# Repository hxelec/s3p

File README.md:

Haase Industries S3P boards: Arduino IDE code and KiCad schematic.

I'll comment the Arduino sketches properly in a few weeks, but,
meanwhile, ask me anything about the code or the schematic on my
YouTube video, and I'll be sure to respond to it.

Here's the video about this project:
https://youtu.be/9oY4NeJDy-g

Thanks to PCBWay for sponsoring this project! Get $5 of New User Free Credit by following this link - https://pcbway.com/g/x5f10h

PCBWay is one of the most experienced PCB manufacturers in China, consider them your one-stop solution that offers PCB fabrication, turn-key PCB Assembly, PCB design, 3D printing, and CNC machining services.

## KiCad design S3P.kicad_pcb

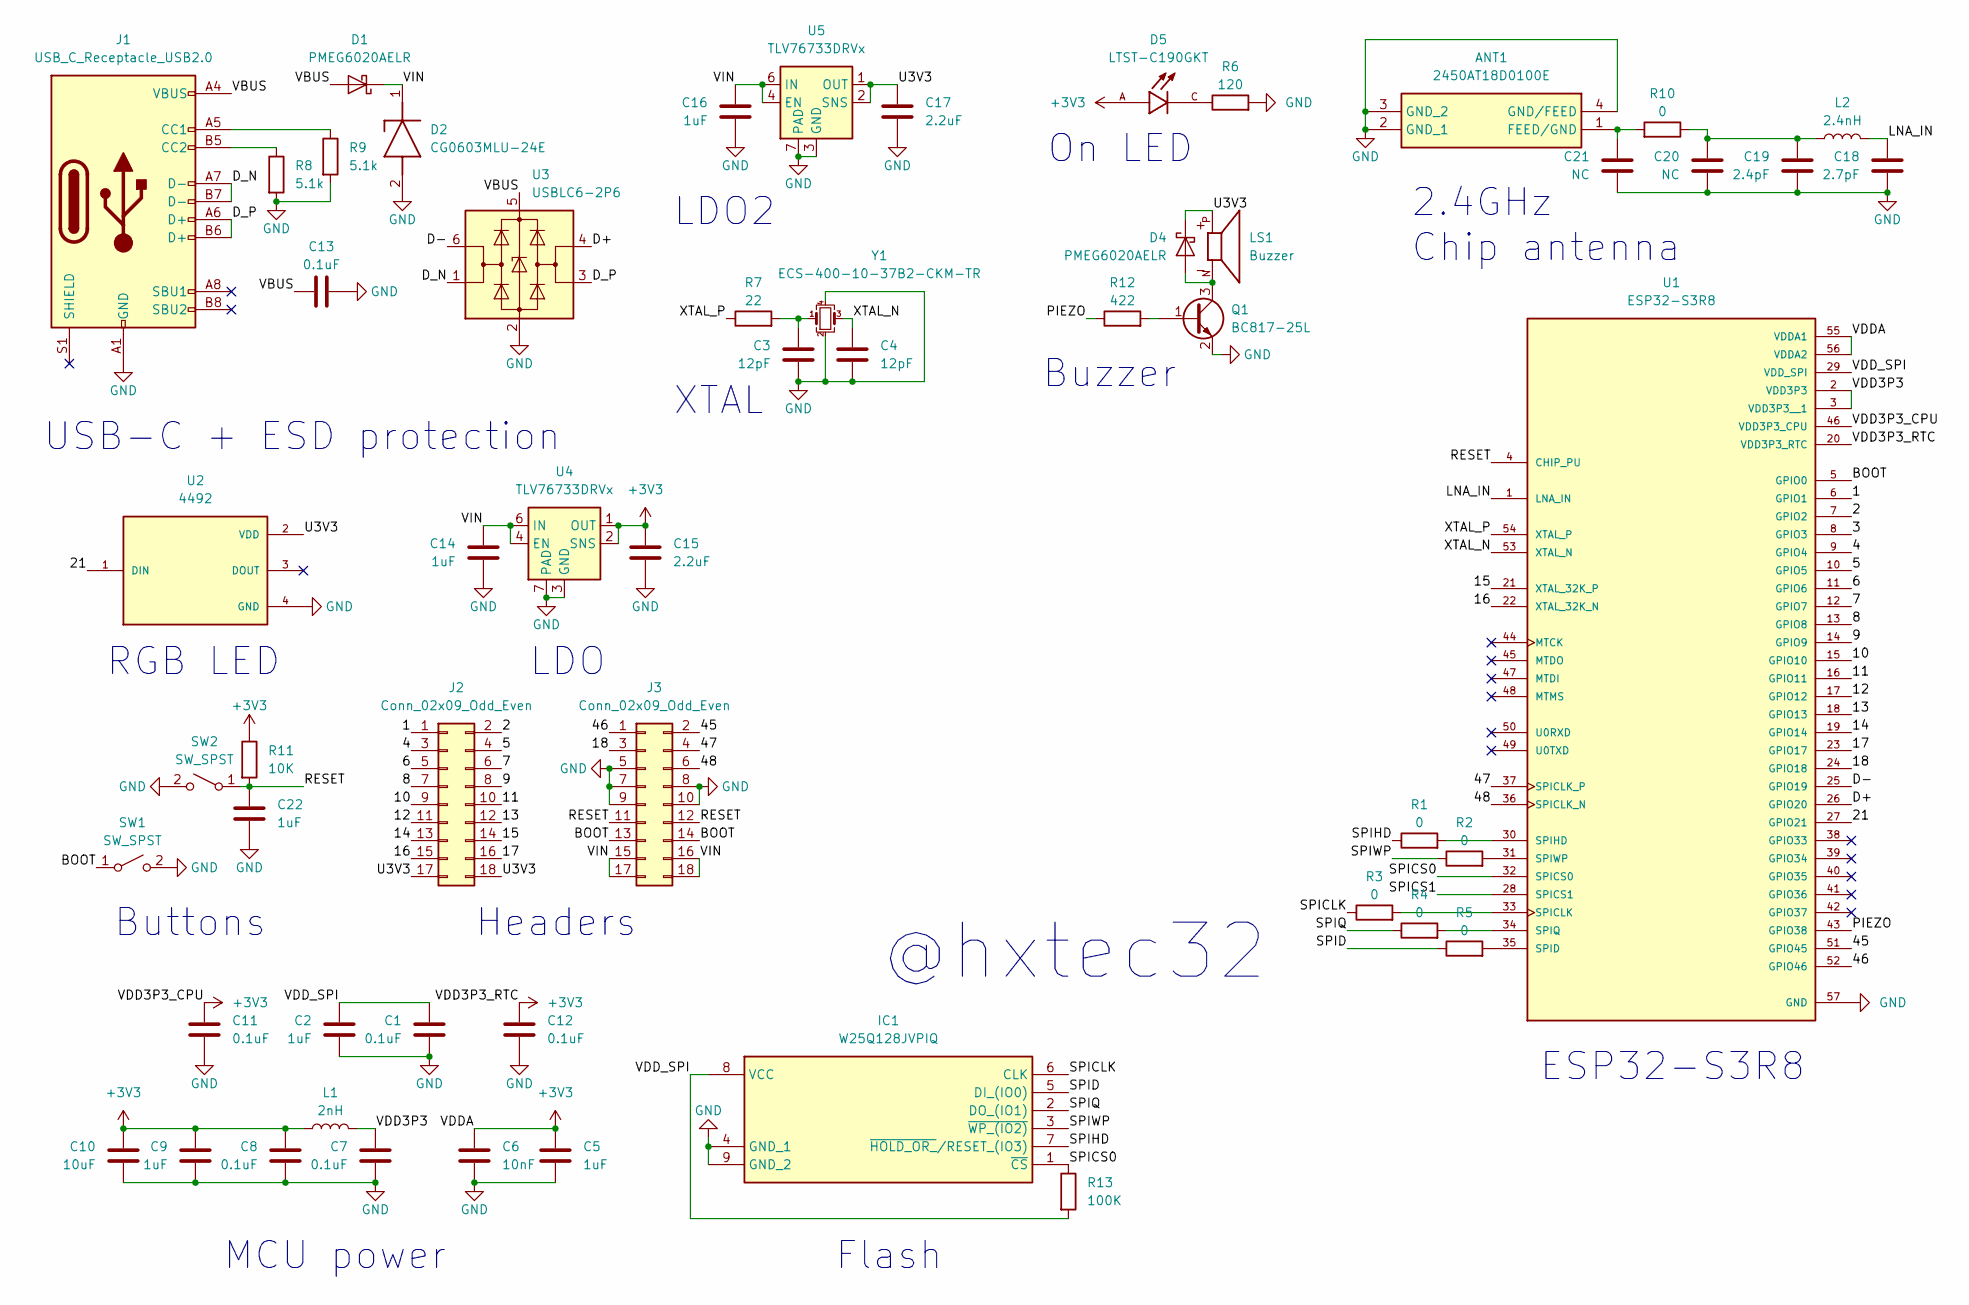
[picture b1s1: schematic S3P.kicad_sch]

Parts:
ANT1: 2450AT18D0100E; Manufacturer_Part_Number 2450AT18D0100E; Mouser Part Number 609-2450AT18D0100E
C1, C7, C8, C11, C12, C13: 0.1uF; R_0402_1005Metric
C2, C5, C9, C22: 1uF; R_0402_1005Metric
C3, C4: 12pF; R_0201_0603Metric
C6: 10nF; R_0201_0603Metric
C10: 10uF; R_0603_1608Metric
C14, C16: 1uF; R_0603_1608Metric
C15, C17: 2.2uF; R_0402_1005Metric
C18: 2.7pF; R_0201_0603Metric
C19: 2.4pF; R_0201_0603Metric
C20, C21: NC; R_0201_0603Metric
D1, D4: PMEG6020AELR; Nexperia_CFP3_SOD-123W
D2: CG0603MLU-24E; DIONC1608X55N; Manufacturer_Part_Number CG0603MLU-24E; Mouser Part Number 652-CG0603MLU-24E
D5: LTST-C190GKT; LEDC1608X35N
IC1: W25Q128JVPIQ; SON127P600X500X80-9N-D; Manufacturer_Part_Number W25Q128JVPIQ; Mouser Part Number 454-W25Q128JVPIQ
J1: USB_C_Receptacle_USB2.0; USB_C_Receptacle_GCT_USB4105-xx-A_16P_TopMnt_Horizontal
J2, J3: Conn_02x09_Odd_Even; PinHeader_2x09_P2.54mm_Vertical
L1: 2nH; L_0402_1005Metric
L2: 2.4nH; L_0201_0603Metric
LS1: Buzzer; XDCR_CMT-0525-75-SMT-TR; PARTREV 1.0
Q1: BC817-25L; SOT-23
R1, R2, R3, R4, R5, R10: 0; R_0201_0603Metric
R6: 120; R_0402_1005Metric
R7: 22; R_0402_1005Metric
R8, R9: 5.1k; R_0402_1005Metric
R11: 10K; R_0402_1005Metric
R12: 422; R_0402_1005Metric
R13: 100K; R_0201_0603Metric
SW1, SW2: SW_SPST; SW_SPST_PTS810
U1: ESP32-S3R8; QFN40P700X700X90-57N-D
U2: 4492; SK6805-EC15; PARTREV 14/10/19
U3: USBLC6-2P6; SOT-666
U4, U5: TLV76733DRVx; WSON-6-1EP_2x2mm_P0.65mm_EP1x1.6mm_ThermalVias
Y1: ECS-400-10-37B2-CKM-TR; Crystal_SMD_2016-4Pin_2.0x1.6mm

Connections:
+3V3: C5.1, C6.1, C8.1, C9.1, C10.1, C11.1, C12.1, C15.1, D5.A, L1.2, R11.1, U1.20 (VDD3P3_RTC), U1.46 (VDD3P3_CPU), U1.55 (VDDA1), U1.56 (VDDA2), U4.1 (OUT), U4.2 (SNS)
/1: J2.1, U1.6 (GPIO1)
/2: J2.2, U1.7 (GPIO2)
/3: U1.8 (GPIO3)
/4: J2.3, U1.9 (GPIO4)
/5: J2.4, U1.10 (GPIO5)
/6: J2.5, U1.11 (GPIO6)
/7: J2.6, U1.12 (GPIO7)
/8: J2.7, U1.13 (GPIO8)
/9: J2.8, U1.14 (GPIO9)
/10: J2.9, U1.15 (GPIO10)
/11: J2.10, U1.16 (GPIO11)
/12: J2.11, U1.17 (GPIO12)
/13: J2.12, U1.18 (GPIO13)
/14: J2.13, U1.19 (GPIO14)
/15: J2.14, U1.21 (XTAL_32K_P)
/16: J2.15, U1.22 (XTAL_32K_N)
/17: J2.16, U1.23 (GPIO17)
/18: J3.3, U1.24 (GPIO18)
/21: U1.27 (GPIO21), U2.1 (DIN)
/45: J3.2, U1.51 (GPIO45)
/46: J3.1, U1.52 (GPIO46)
/47: J3.4, U1.37 (SPICLK_P)
/48: J3.6, U1.36 (SPICLK_N)
/BOOT: J3.13, J3.14, SW1.1 (A), U1.5 (GPIO0)
/D+: U1.26 (GPIO20), U3.4 (I/O2)
/D-: U1.25 (GPIO19), U3.6 (I/O1)
/D_N: J1.A7 (D-), J1.B7 (D-), U3.1 (I/O1)
/D_P: J1.A6 (D+), J1.B6 (D+), U3.3 (I/O2)
/LNA_IN: C18.1, L2.1, U1.1 (LNA_IN)
/PIEZO: R12.1, U1.43 (GPIO38)
/RESET: C22.1, J3.11, J3.12, R11.2, SW2.1 (A), U1.4 (CHIP_PU)
/SPICLK: IC1.6 (CLK), R3.1
/SPICS0: IC1.1 (~CS), R13.1, U1.32 (SPICS0)
/SPICS1: U1.28 (SPICS1)
/SPID: IC1.5 (DI_(IO0)), R5.1
/SPIHD: IC1.7 (~HOLD_OR_/RESET_(IO3)), R1.1
/SPIQ: IC1.2 (DO_(IO1)), R4.1
/SPIWP: IC1.3 (~WP_(IO2)), R2.1
/U3V3: C17.1, D4.1 (K), J2.17, J2.18, LS1.P, U2.2 (VDD), U5.1 (OUT), U5.2 (SNS)
/VBUS: C13.1, D1.2 (A), J1.A4 (VBUS), J1.A9 (VBUS), J1.B4 (VBUS), J1.B9 (VBUS), U3.5 (VBUS)
/VDD3P3: C7.1, L1.1, U1.2 (VDD3P3), U1.3 (VDD3P3__1)
/VDD_SPI: C1.1, C2.1, IC1.8 (VCC), R13.2, U1.29 (VDD_SPI)
/VIN: C14.1, C16.1, D1.1 (K), D2.1 (K), J3.15, J3.16, J3.17, J3.18, U4.4 (EN), U4.6 (IN), U5.4 (EN), U5.6 (IN)
/XTAL_N: C4.1, U1.53 (XTAL_N), Y1.3
/XTAL_P: R7.1, U1.54 (XTAL_P)
GND: ANT1.2 (GND_1), ANT1.3 (GND_2), ANT1.4 (GND/FEED), C1.2, C2.2, C3.2, C4.2, C5.2, C6.2, C7.2, C8.2, C9.2, C10.2, C11.2, C12.2, C13.2, C14.2, C15.2, C16.2, C17.2, C18.2, C19.2, C20.2, C21.2, C22.2, D2.2 (A), IC1.4 (GND_1), IC1.9 (GND_2), J1.A1 (GND), J1.A12 (GND), J1.B1 (GND), J1.B12 (GND), J3.5, J3.7, J3.8, J3.9, J3.10, Q1.2 (E), R6.2, R8.2, R9.2, SW1.2 (B), SW2.2 (B), U1.57 (GND), U2.4 (GND), U3.2 (GND), U4.3 (GND), U4.5 (GND), U4.7 (PAD), U5.3 (GND), U5.5 (GND), U5.7 (PAD), Y1.2, Y1.4
unnamed: ANT1.1 (FEED/GND), C21.1, R10.2
unnamed: C3.1, R7.2, Y1.1
unnamed: C19.1, C20.1, L2.2, R10.1
unnamed: D4.2 (A), LS1.N, Q1.3 (C)
unnamed: D5.C, R6.1
unnamed: J1.A5 (CC1), R9.1
unnamed: J1.B5 (CC2), R8.1
unnamed: Q1.1 (B), R12.2
unnamed: R3.2, U1.33 (SPICLK)
unnamed: R5.2, U1.35 (SPID)
unnamed: R1.2, U1.30 (SPIHD)
unnamed: R4.2, U1.34 (SPIQ)
unnamed: R2.2, U1.31 (SPIWP)

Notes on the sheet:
LDO
Buzzer
Buttons
RGB LED
Flash
USB-C + ESD protection
Chip antenna
Headers
XTAL
@hxtec32
MCU power
On LED
2.4GHz
ESP32-S3R8
LDO2

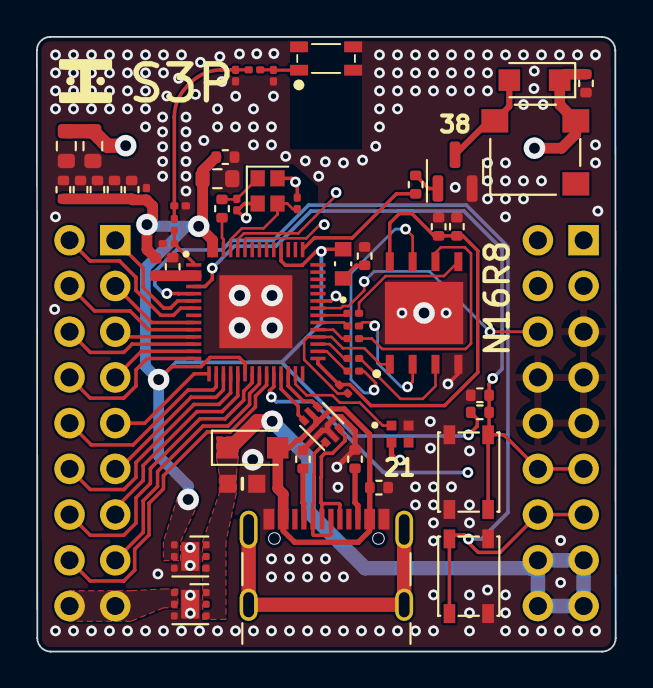
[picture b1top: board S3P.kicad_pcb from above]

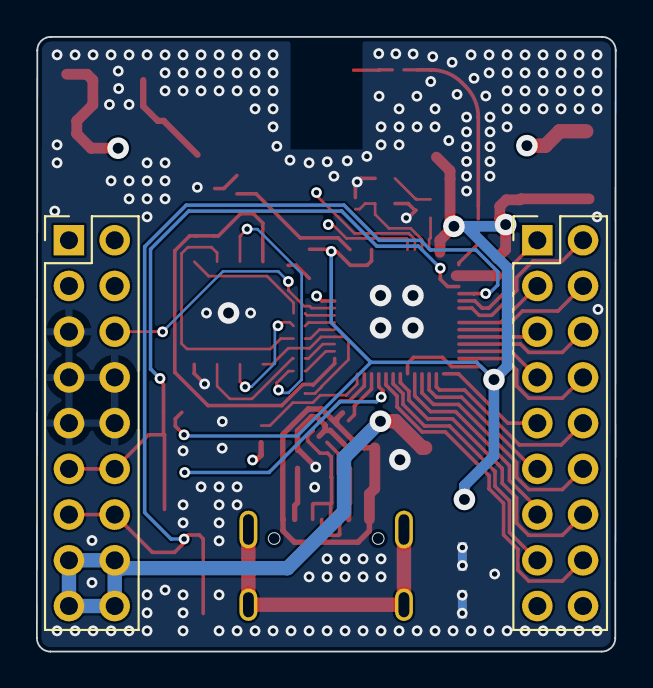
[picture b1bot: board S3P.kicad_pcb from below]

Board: 4 copper layers, 32.2 x 34.1 mm, 56 parts (2 on the bottom side), 58 nets.

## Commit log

2024-01-25 Add files via upload
    oopsies, sorry for forgetting to upload the schematic
2024-02-05 Create LICENSE
2024-04-10 KICAD FILES
